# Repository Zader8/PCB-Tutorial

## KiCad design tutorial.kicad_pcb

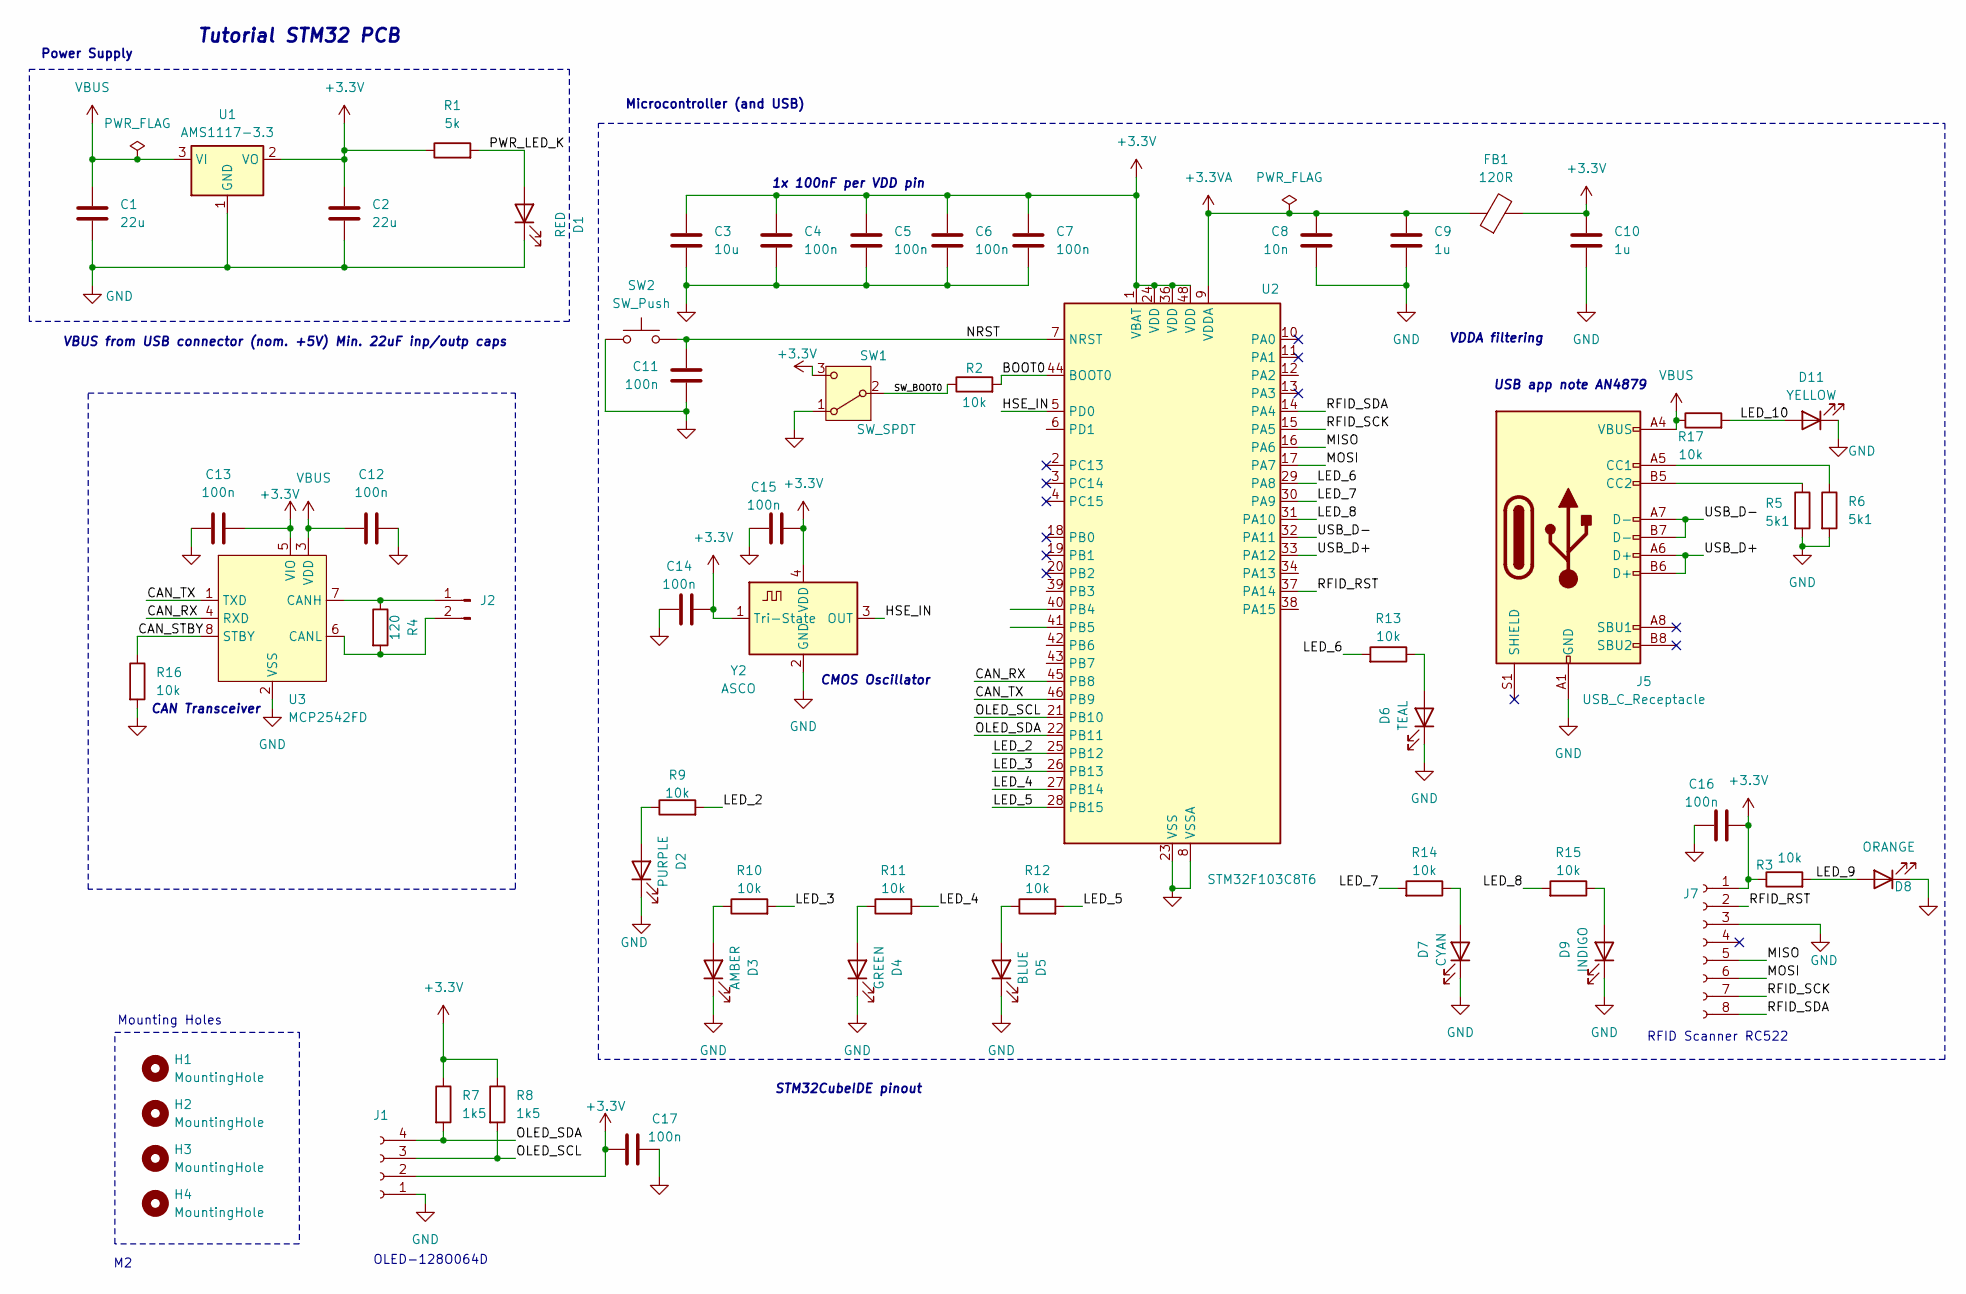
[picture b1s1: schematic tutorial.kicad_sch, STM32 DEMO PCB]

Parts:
C1, C2: 22u; C_0805_2012Metric
C3: 10u; C_0603_1608Metric
C4, C5, C6, C7, C11, C12, C13, C14, C15, C16, C17: 100n; C_0603_1608Metric
C8: 10n; C_0603_1608Metric
C9, C10: 1u; C_0603_1608Metric
D1: RED; LED_0603_1608Metric
D2: PURPLE; LED_0603_1608Metric
D3: AMBER; LED_0603_1608Metric
D4: GREEN; LED_0603_1608Metric
D5: BLUE; LED_0603_1608Metric
D6: TEAL; LED_0603_1608Metric
D7: CYAN; LED_0603_1608Metric
D8: ORANGE; LED_0603_1608Metric
D9: INDIGO; LED_0603_1608Metric
D11: YELLOW; LED_0603_1608Metric
FB1: 120R; L_0805_2012Metric
H1, H2, H3, H4: MountingHole; MountingHole_2.2mm_M2
J1: Conn_01x04_Socket; Display_128x64_096_I2C
J2: Conn_01x02_Pin; PinHeader_1x02_P2.54mm_Vertical
J5: USB_C_Receptacle; USB_C_Receptacle_GCT_USB4105-xx-A_16P_TopMnt_Horizontal
J7: Conn_01x08_Socket; PinSocket_1x08_P2.54mm_Vertical
R1: 5k; R_0603_1608Metric
R2, R3, R9, R10, R11, R12, R13, R14, R15, R16, R17: 10k; R_0603_1608Metric
R4: 120; R_0603_1608Metric
R5, R6: 5k1; R_0603_1608Metric
R7, R8: 1k5; R_0603_1608Metric
SW1: SW_SPDT; SW_SPDT_PCM12
SW2: SW_Push; SW_PUSH_6mm_H5mm
U1: AMS1117-3.3; SOT-223-3_TabPin2
U2: STM32F103C8T6; LQFP-48_7x7mm_P0.5mm
U3: MCP2542FD; SOIC-8_3.9x4.9mm_P1.27mm
Y2: ASCO; Crystal_SMD_3225-4Pin_3.2x2.5mm

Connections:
+3.3V: C2.1, C3.1, C4.1, C5.1, C6.1, C7.1, C10.1, C13.2, C14.2, C15.2, C16.2, C17.2, FB1.2, J1.2, J7.1, R1.1, R3.1, R7.1, R8.1, SW1.3 (C), U1.2 (VO), U2.1 (VBAT), U2.24 (VDD), U2.36 (VDD), U2.48 (VDD), U3.5 (VIO), Y2.1 (Tri-State), Y2.4 (VDD)
+3.3VA: C8.1, C9.1, FB1.1, U2.9 (VDDA)
/BOOT0: R2.2, U2.44 (BOOT0)
/CAN_RX: U2.45 (PB8), U3.4 (RXD)
/CAN_STBY: R16.1, U3.8 (STBY)
/CAN_TX: U2.46 (PB9), U3.1 (TXD)
/HSE_IN: U2.5 (PD0), Y2.3 (OUT)
/LED_2: R9.2, U2.25 (PB12)
/LED_3: R10.2, U2.26 (PB13)
/LED_4: R11.2, U2.27 (PB14)
/LED_5: R12.2, U2.28 (PB15)
/LED_6: R13.2, U2.29 (PA8)
/LED_7: R14.2, U2.30 (PA9)
/LED_8: R15.2, U2.31 (PA10)
/LED_9: D8.2 (A), R3.2
/LED_10: D11.2 (A), R17.2
/MISO: J7.5, U2.16 (PA6)
/MOSI: J7.6, U2.17 (PA7)
/NRST: C11.1, SW2.2, U2.7 (NRST)
/OLED_SCL: J1.3, R8.2, U2.21 (PB10)
/OLED_SDA: J1.4, R7.2, U2.22 (PB11)
/PWR_LED_K: D1.2 (A), R1.2
/RFID_RST: J7.2, U2.37 (PA14)
/RFID_SCK: J7.7, U2.15 (PA5)
/RFID_SDA: J7.8, U2.14 (PA4)
/SW_BOOT0: R2.1, SW1.2 (B)
/USB_D+: J5.A6 (D+), J5.B6 (D+), U2.33 (PA12)
/USB_D-: J5.A7 (D-), J5.B7 (D-), U2.32 (PA11)
GND: C1.2, C2.2, C3.2, C4.2, C5.2, C6.2, C7.2, C8.2, C9.2, C10.2, C11.2, C12.2, C13.1, C14.1, C15.1, C16.1, C17.1, D1.1 (K), D2.1 (K), D3.1 (K), D4.1 (K), D5.1 (K), D6.1 (K), D7.1 (K), D8.1 (K), D9.1 (K), D11.1 (K), J1.1, J5.A1 (GND), J5.A12 (GND), J5.B1 (GND), J5.B12 (GND), J7.3, R5.2, R6.2, R16.2, SW1.1 (A), SW2.1, U1.1 (GND), U2.8 (VSSA), U2.23 (VSS), U2.35 (VSS), U2.47 (VSS), U3.2 (VSS), Y2.2 (GND)
unnamed: D2.2 (A), R9.1
unnamed: D3.2 (A), R10.1
unnamed: D4.2 (A), R11.1
unnamed: D5.2 (A), R12.1
unnamed: D6.2 (A), R13.1
unnamed: D7.2 (A), R14.1
unnamed: D9.2 (A), R15.1
unnamed: J2.1, R4.1, U3.7 (CANH)
unnamed: J2.2, R4.2, U3.6 (CANL)
unnamed: J5.A5 (CC1), R6.1
unnamed: J5.B5 (CC2), R5.1
VBUS: C1.1, C12.1, J5.A4 (VBUS), J5.A9 (VBUS), J5.B4 (VBUS), J5.B9 (VBUS), R17.1, U1.3 (VI), U3.3 (VDD)

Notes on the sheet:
VDDA filtering
Microcontroller (and USB)
1x 100nF per VDD pin
CMOS Oscillator
VBUS from USB connector (nom. +5V) Min. 22uF inp/outp caps
STM32CubeIDE pinout
RFID Scanner RC522
CAN Transceiver
OLED-128O064D
Tutorial STM32 PCB
Mounting Holes
USB app note AN4879
Power Supply

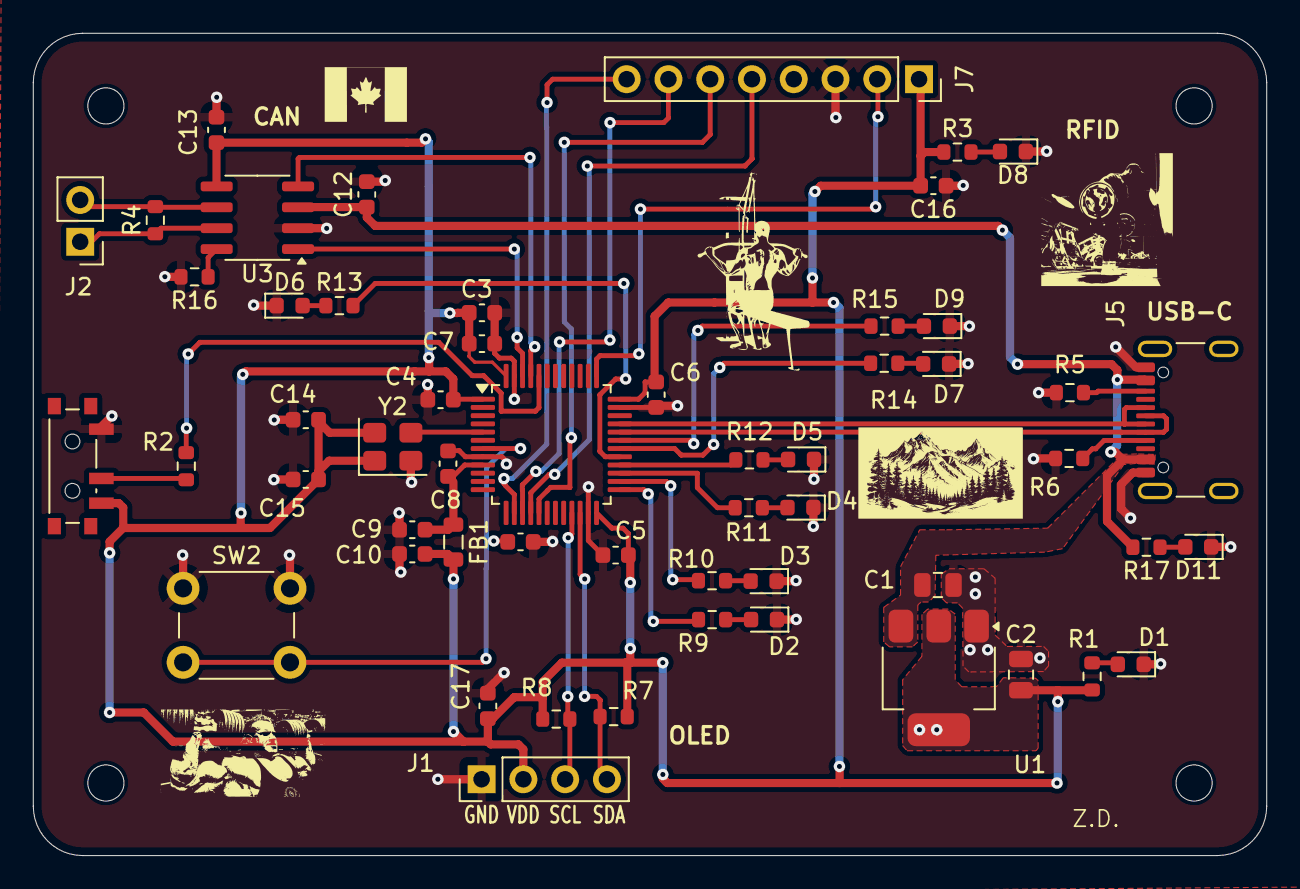
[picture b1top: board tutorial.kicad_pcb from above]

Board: 2 copper layers, 75.0 x 50.0 mm, 59 parts (0 on the bottom side), 41 nets.

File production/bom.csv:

Designator,Footprint,Quantity,Value,LCSC Part #
"C1, C2",0805,2,22u,
"C10, C9",0603,2,1u,
"C11, C12, C13, C14, C15, C16, C17, C4, C5, C6, C7",0603,11,100n,
C3,0603,1,10u,
C8,0603,1,10n,
D1,0603,1,RED,
D11,0603,1,YELLOW,
D2,0603,1,PURPLE,
D3,0603,1,AMBER,
D4,0603,1,GREEN,
D5,0603,1,BLUE,
D6,0603,1,TEAL,
D7,0603,1,CYAN,
D8,0603,1,ORANGE,
D9,0603,1,INDIGO,
FB1,0805,1,120R,
J1,Display_128x64_096_I2C,1,Conn_01x04_Socket,
J2,PinHeader_1x02_P2.54mm_Vertical,1,Conn_01x02_Pin,
J5,USB_C_Receptacle_GCT_USB4105-xx-A_16P_TopMnt_Horizontal,1,USB_C_Receptacle,
J7,PinSocket_1x08_P2.54mm_Vertical,1,Conn_01x08_Socket,
R1,0603,1,5k,
"R10, R11, R12, R13, R14, R15, R16, R17, R2, R3, R9",0603,11,10k,
R4,0603,1,120,
"R5, R6",0603,2,5k1,
"R7, R8",0603,2,1k5,
SW1,SW_SPDT_PCM12,1,SW_SPDT,
SW2,SW_PUSH_6mm_H5mm,1,SW_Push,
U1,SOT-223-3_TabPin2,1,AMS1117-3.3,
U2,LQFP-48_7x7mm_P0.5mm,1,STM32F103C8T6,
U3,SOIC-8_3.9x4.9mm_P1.27mm,1,MCP2542FD,
Y2,Crystal_SMD_3225-4Pin_3.2x2.5mm,1,ASCO,

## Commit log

2025-10-29 silk screen
2025-11-01 Revised, added silkscreen
2025-11-01 Gerber files
2025-11-01 Fix RFID pinout
